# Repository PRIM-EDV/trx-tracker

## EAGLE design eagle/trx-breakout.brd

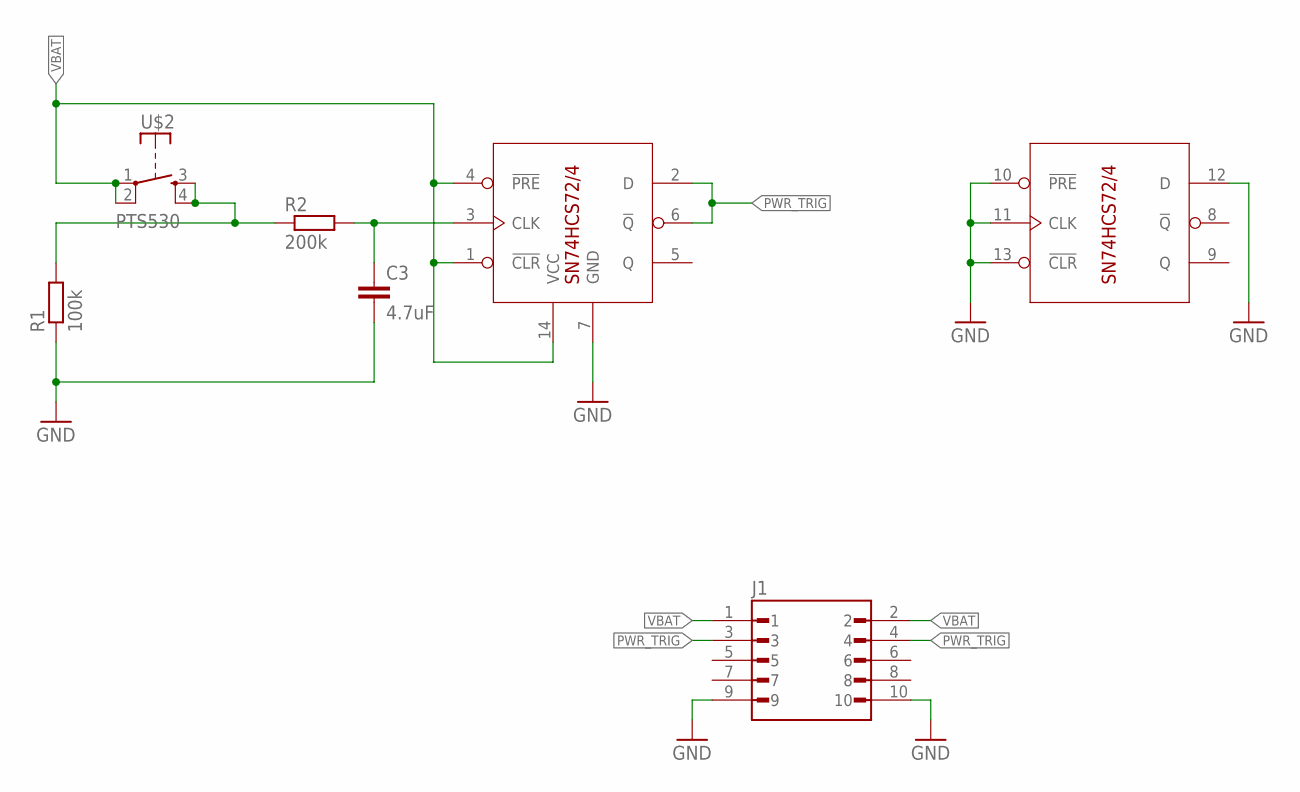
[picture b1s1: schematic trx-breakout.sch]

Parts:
C3: 4.7uF; C0805
J1: DF12NB(3.0)-10DX-0.5VHRS_DF12NB(3.0)-10DS-0.5V; HRS_DF12NB(3.0)-10DS-0.5V
R1: 100k; R0805
R2: 200k; R0805
U$1: SN74HCS72/4; TSSOP14
U$2: PTS530

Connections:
GND: C3.2, J1.9, J1.10, R1.1, U$1.7 (GND), U$1.10 (!PRE), U$1.11 (CLK), U$1.12 (D), U$1.13 (!CLR)
unnamed: C3.1, R2.2, U$1.3 (CLK)
unnamed: R1.2, R2.1, U$2.3 (S), U$2.4 (S)
PWR_TRIG: J1.3, J1.4, U$1.2 (D), U$1.6 (!Q)
VBAT: J1.1, J1.2, U$1.1 (!CLR), U$1.4 (!PRE), U$1.14 (VCC), U$2.1, U$2.2

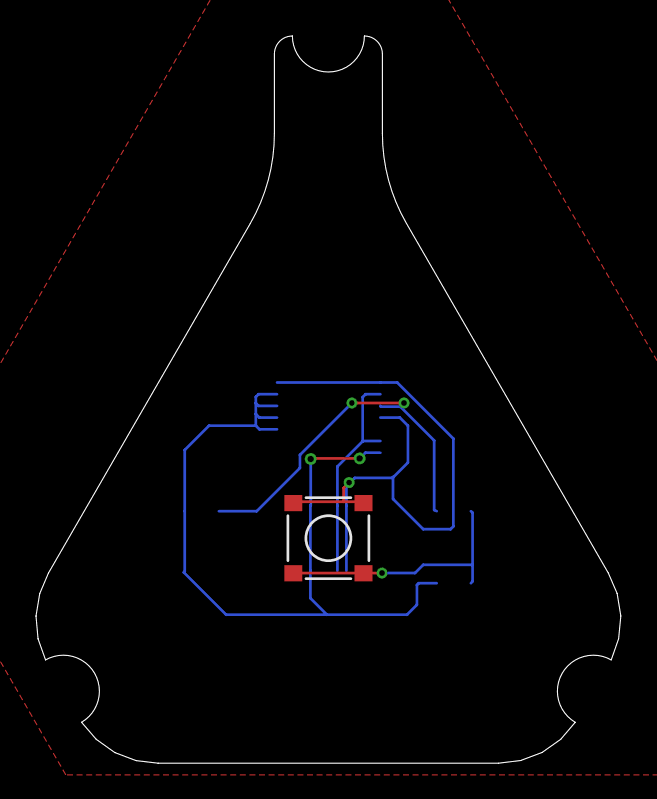
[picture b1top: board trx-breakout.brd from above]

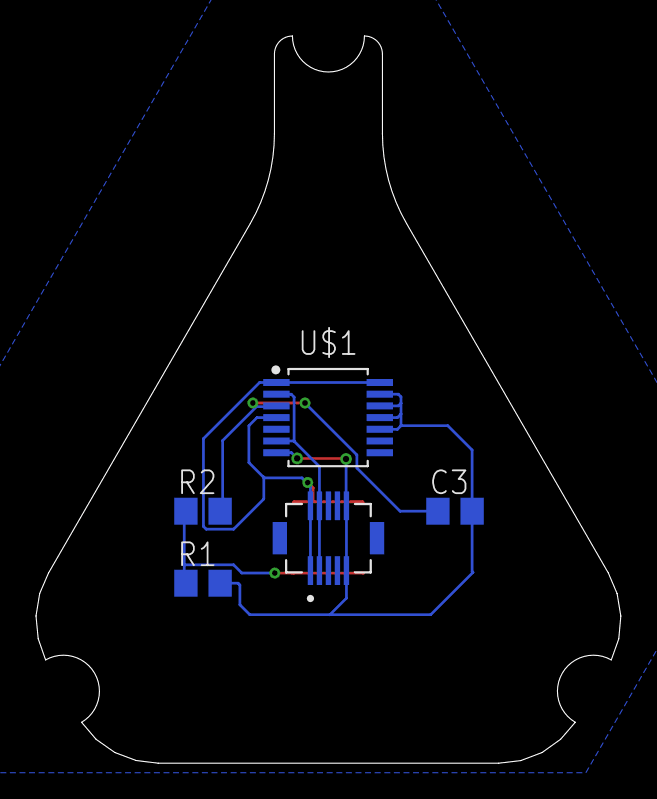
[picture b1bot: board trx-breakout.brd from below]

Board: 2 copper layers, 32.5 x 40.4 mm, 6 parts (5 on the bottom side), 5 nets.

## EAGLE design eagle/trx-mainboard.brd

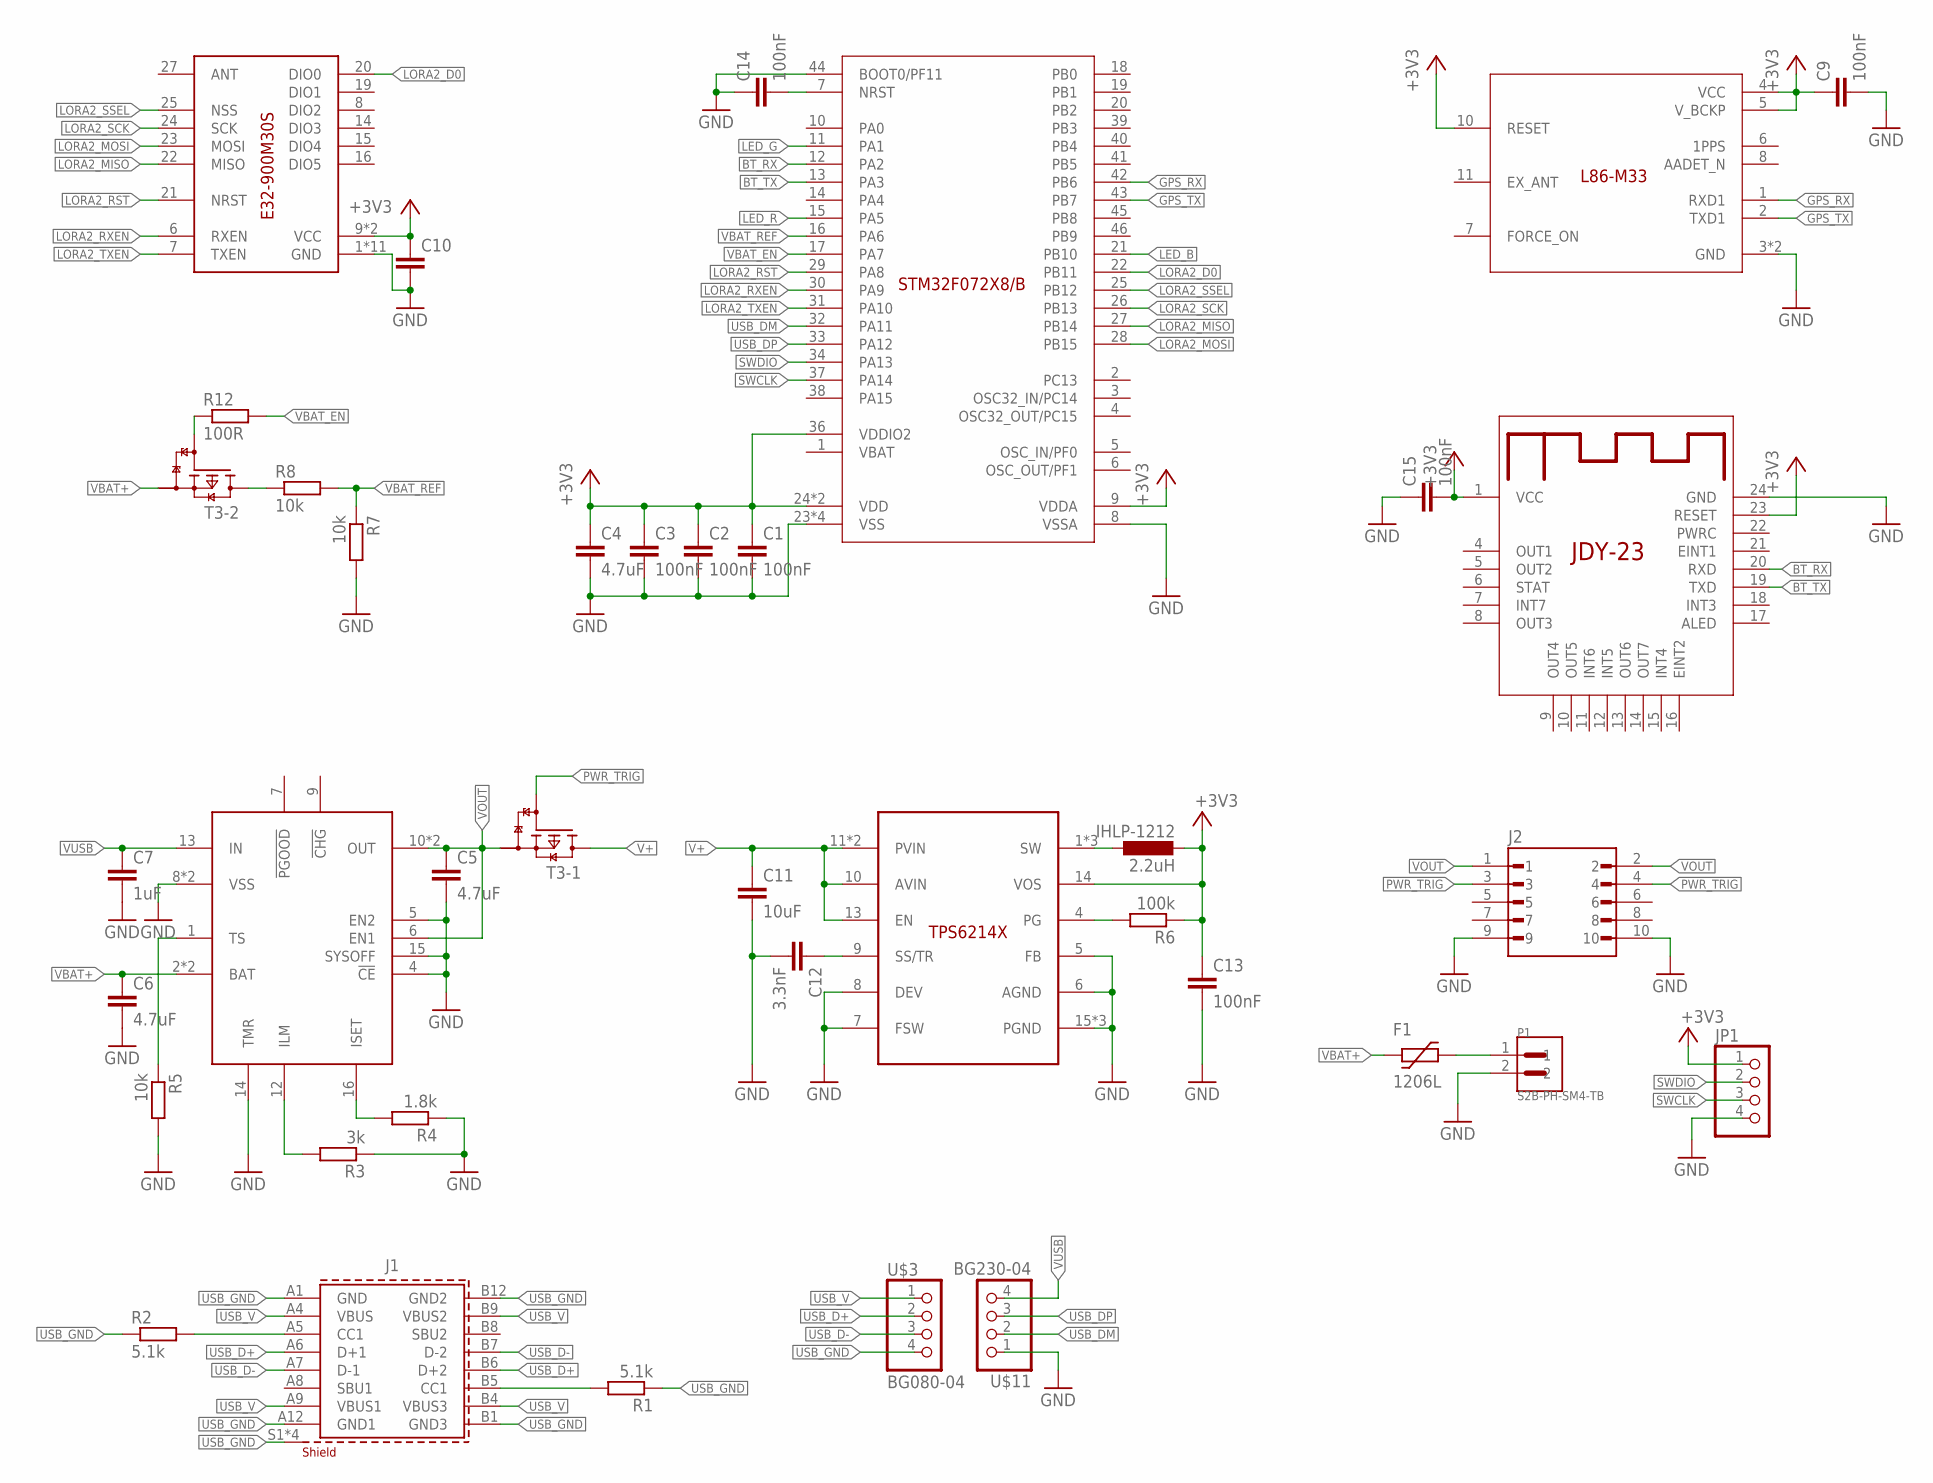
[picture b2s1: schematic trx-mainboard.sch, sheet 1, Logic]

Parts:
C1, C2, C3, C9, C13, C14, C15: 100nF; C0805
C4, C5, C6, C10: 4.7uF; C0805
C7: 1uF; C0805
C11: 10uF; C0805
C12: 3.3nF; C0805
F1: 1206L
J1: 629722000214
J2: DF12NB(3.0)-10DP-0.5V; HRS_DF12NB(3.0)-10DP-0.5V
JP1: PINHD-1X04_2.54-SMD; 1X04SMD
P1: S2B-PH-SM4-TB; JST_S2B-PH-SM4-TB
R1, R2: 5.1k; R0805
R3: 3k; R0805
R4: 1.8k; R0805
R5, R7, R8: 10k; R0805
R6: 100k; R0805
R12: 100R; R0805
T3: NX3008PBKS; SOT363
U2: BQ2407X; VQFN16-3X3
U$1: L86-M33
U$2: TPS6214X; VQFN16-3X3
U$3: BG080-04; P-1X4/90-2.54X1.50MMX2.54MM-SMT
U$4: IHLP-1212; 1212BZ
U$5: JDY-23
U$10: STM32-F072X8/B-48; UFQFPN48-7X7
U$11: BG230-04; S-1X4/90-2.54MM-SMT
U$14: E32-900M30S

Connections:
+3V3: C1.1, C2.1, C3.1, C4.1, C9.1, C10.1, C13.1, C15.2, JP1.1, R6.1, U$1.4 (VCC), U$1.5 (V_BCKP), U$1.10 (RESET), U$2.14 (VOS), U$4.2, U$5.1 (VCC), U$5.23 (RESET), U$10.9 (VDDA), U$10.24 (VDD), U$10.36 (VDDIO2), U$10.48 (VDD), U$14.9 (VCC), U$14.10 (VCC); also elsewhere on the board
BT_RX: U$5.20 (RXD), U$10.12 (PA2)
BT_TX: U$5.19 (TXD), U$10.13 (PA3)
GND: C1.2, C2.2, C3.2, C4.2, C5.2, C6.2, C7.2, C9.2, C10.2, C11.2, C12.2, C13.2, C14.1, C15.1, J2.9, J2.10, JP1.4, P1.2, R3.1, R4.1, R5.2, R7.2, U2.4 (!CE), U2.5 (EN2), U2.8 (VSS), U2.14 (TMR), U2.15 (SYSOFF), U2.17 (VSS), U$1.3 (GND), U$1.12 (GND), U$2.5 (FB), U$2.6 (AGND), U$2.7 (FSW), U$2.8 (DEV), U$2.15 (PGND), U$2.16 (PGND), U$2.17 (PGND), U$5.24 (GND), U$10.8 (VSSA), U$10.23 (VSS), U$10.35 (VSS), U$10.44 (BOOT0/PF11), U$10.47 (VSS), U$10.P$49 (VSS), U$11.1, U$14.1 (GND), U$14.2 (GND), U$14.3 (GND), U$14.4 (GND), U$14.5 (GND), U$14.11 (GND), U$14.12 (GND), U$14.17 (GND), U$14.18 (GND), U$14.26 (GND), U$14.28 (GND); also elsewhere on the board
GPS_RX: U$1.1 (RXD1), U$10.42 (PB6)
GPS_TX: U$1.2 (TXD1), U$10.43 (PB7)
LED_B: U$10.21 (PB10); also elsewhere on the board
LED_G: U$10.11 (PA1); also elsewhere on the board
LED_R: U$10.15 (PA5); also elsewhere on the board
LORA2_D0: U$10.22 (PB11), U$14.20 (DIO0)
LORA2_MISO: U$10.27 (PB14), U$14.22 (MISO)
LORA2_MOSI: U$10.28 (PB15), U$14.23 (MOSI)
LORA2_RST: U$10.29 (PA8), U$14.21 (NRST)
LORA2_RXEN: U$10.30 (PA9), U$14.6 (RXEN)
LORA2_SCK: U$10.26 (PB13), U$14.24 (SCK)
LORA2_SSEL: U$10.25 (PB12), U$14.25 (NSS)
LORA2_TXEN: U$10.31 (PA10), U$14.7 (TXEN)
unnamed: J1.A5 (CC1), R2.2
unnamed: J1.B5 (CC1), R1.2
unnamed: R3.2, U2.12 (ILM)
unnamed: R4.2, U2.16 (ISET)
unnamed: R5.1, U2.1 (TS)
unnamed: U$2.1 (SW), U$2.2 (SW), U$2.3 (SW), U$4.1
unnamed: C12.1, U$2.9 (SS/TR)
unnamed: R6.2, U$2.4 (PG)
unnamed: C14.2, U$10.7 (NRST)
unnamed: F1.P$2 (2), P1.1
unnamed: R8.1, T3.3 (D)
unnamed: R12.1, T3.5 (G)
PWR_TRIG: J2.3, J2.4, T3.2 (G)
SWCLK: JP1.3, U$10.37 (PA14)
SWDIO: JP1.2, U$10.34 (PA13)
USB_D+: J1.A6 (D+1), J1.B6 (D+2), U$3.2
USB_D-: J1.A7 (D-1), J1.B7 (D-2), U$3.3
USB_DM: U$10.32 (PA11), U$11.2
USB_DP: U$10.33 (PA12), U$11.3
USB_GND: J1.A1 (GND), J1.A12 (GND1), J1.B1 (GND3), J1.B12 (GND2), J1.S1 (SHIELD), J1.S2 (SHIELD), J1.S3 (SHIELD), J1.S4 (SHIELD), R1.1, R2.1, U$3.4
USB_V: J1.A4 (VBUS), J1.A9 (VBUS1), J1.B4 (VBUS3), J1.B9 (VBUS2), U$3.1
V+: C11.1, T3.6 (D), U$2.10 (AVIN), U$2.11 (PVIN), U$2.12 (PVIN), U$2.13 (EN)
VBAT+: C6.1, F1.P$1 (1), T3.4 (S), U2.2 (BAT), U2.3 (BAT)
VBAT_EN: R12.2, U$10.17 (PA7)
VBAT_REF: R7.1, R8.2, U$10.16 (PA6)
VOUT: C5.1, J2.1, J2.2, T3.1 (S), U2.6 (EN1), U2.10 (OUT), U2.11 (OUT)
VUSB: C7.1, U2.13 (IN), U$11.4

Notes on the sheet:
2.2uH

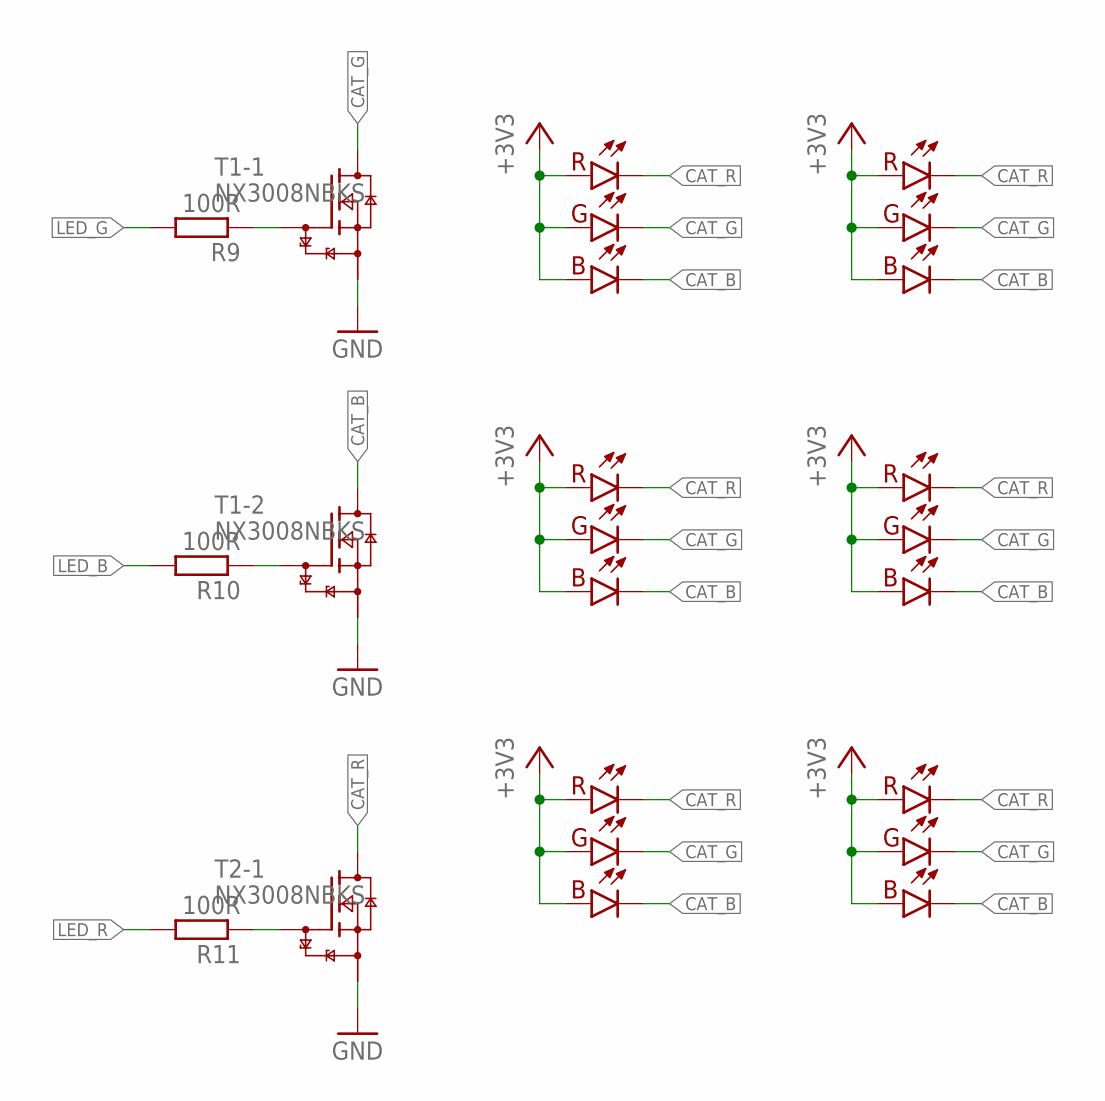
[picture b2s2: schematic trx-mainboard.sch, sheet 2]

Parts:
R9, R10, R11: 100R; R0805
T1, T2: NX3008NBKS; SOT363
U$6, U$7, U$8, U$9, U$12, U$13: RGB_LED; PLCC6

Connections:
+3V3: U$6.1 (A.B), U$6.3 (A.R), U$6.5 (A.G), U$7.1 (A.B), U$7.3 (A.R), U$7.5 (A.G), U$8.1 (A.B), U$8.3 (A.R), U$8.5 (A.G), U$9.1 (A.B), U$9.3 (A.R), U$9.5 (A.G), U$12.1 (A.B), U$12.3 (A.R), U$12.5 (A.G), U$13.1 (A.B), U$13.3 (A.R), U$13.5 (A.G); also elsewhere on the board
CAT_B: T1.3 (D), U$6.2 (C.B), U$7.2 (C.B), U$8.2 (C.B), U$9.2 (C.B), U$12.2 (C.B), U$13.2 (C.B)
CAT_G: T1.6 (D), U$6.6 (C.G), U$7.6 (C.G), U$8.6 (C.G), U$9.6 (C.G), U$12.6 (C.G), U$13.6 (C.G)
CAT_R: T2.6 (D), U$6.4 (C.R), U$7.4 (C.R), U$8.4 (C.R), U$9.4 (C.R), U$12.4 (C.R), U$13.4 (C.R)
GND: T1.1 (S), T1.4 (S), T2.1 (S); also elsewhere on the board
LED_B: R10.2; also elsewhere on the board
LED_G: R9.2; also elsewhere on the board
LED_R: R11.2; also elsewhere on the board
unnamed: R9.1, T1.2 (G)
unnamed: R10.1, T1.5 (G)
unnamed: R11.1, T2.2 (G)

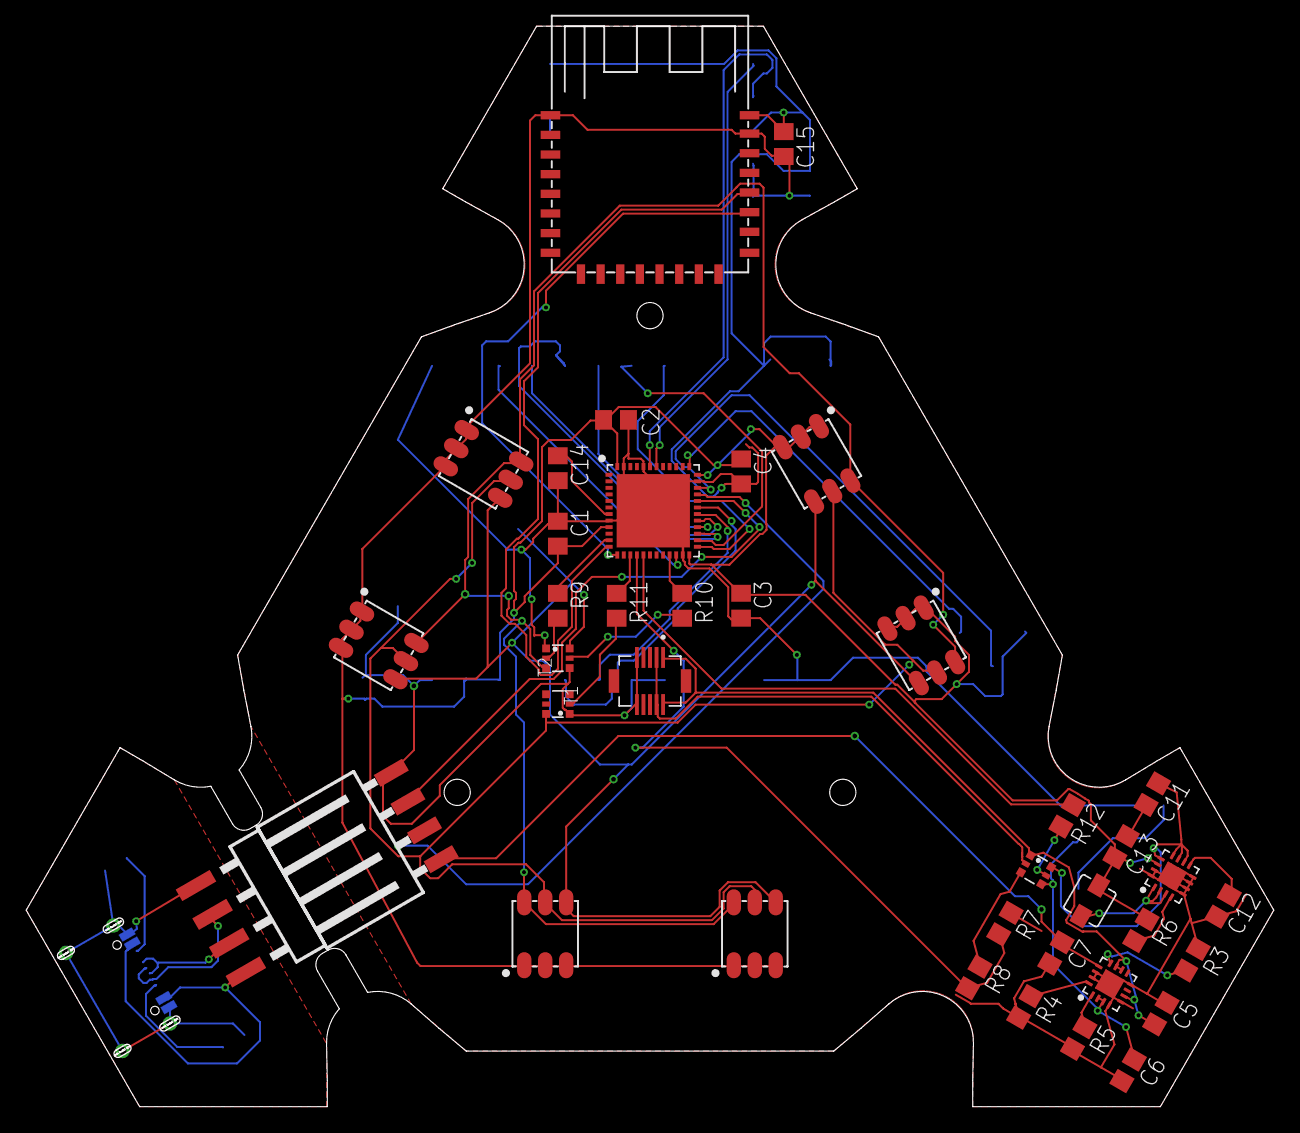
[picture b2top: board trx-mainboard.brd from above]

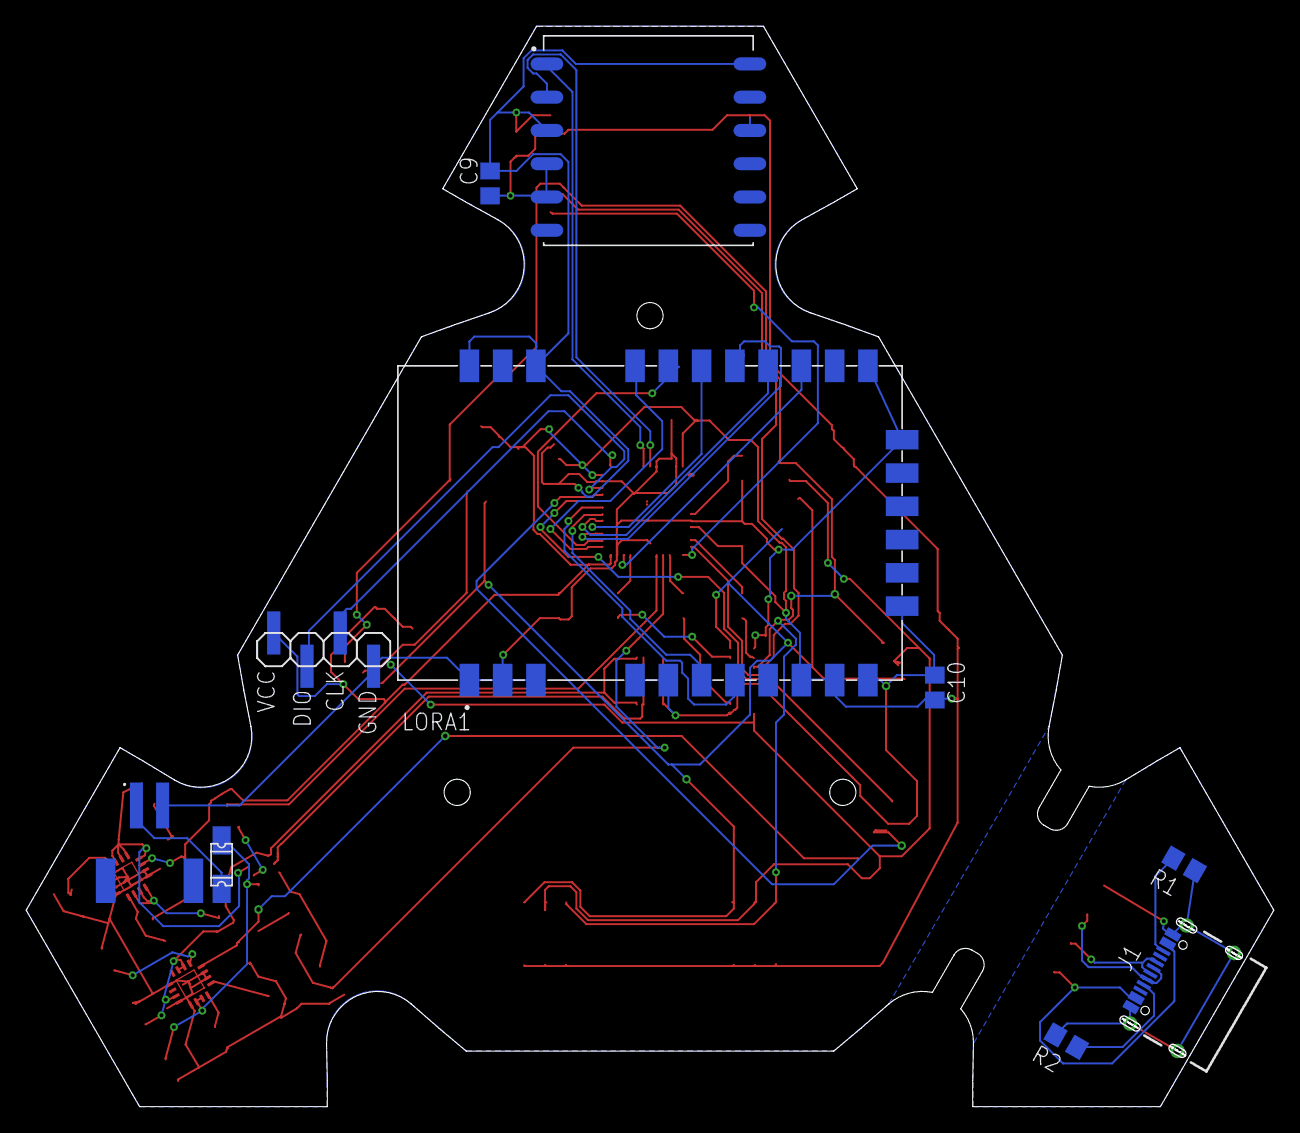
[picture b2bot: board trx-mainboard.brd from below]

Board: 2 copper layers, 95.2 x 82.4 mm, 49 parts (10 on the bottom side), 50 nets.

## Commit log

2022-09-17 Added initial dat
2023-05-01 Added eagle files and gitignore
2023-05-01 Added display pinheader
2023-05-02 Changed board layout
2023-05-08 Added further components to pcb
2023-07-02 Added breakout board and progressed mainboard
2023-07-02 updated modm
2023-07-04 Added basic auto-route
2023-07-16 Finalized alpha design
2023-08-17 Added firmware boilerplate
2023-08-17 Added new layout and gerber files
2023-08-20 Added basic usb serial implementation
2023-08-25 Designed new boards wit fixed errors
2023-08-25 Added basic functionality
2023-09-21 Reworked breakout board
2024-02-08 Modified board layout
2024-03-21 Adjusted settings for trx version
2024-03-26 Fixed Pin Settings and power control of E32 module
2024-05-01 Added wait to TX
2024-05-01 renamed lora namespace
2024-05-04 Added nanopb protocol boilerplate and led driver boilerplate
2024-05-05 Added preliminary led driver
2024-05-05 Added lora timeouts
2025-08-02 Added preliminary csma
2025-08-02 Added missing DIO mapping for CAD mode
2025-08-02 Added preliminary battery adc
2025-08-25 Added adc conversion for battery monitoring
2025-08-27 Added preliminary bluetooth gateway
2025-08-28 Prepared protobuf protocol implementation
2025-08-29 Added nanopb string decode callback

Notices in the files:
parts and their libraries:
Wurth_Connectors_WR-USB: Copyright: Würth Elektronik
NXP_60_26022015: This library may be distributed and adapted freely for any purpose, as long as NXP is credited and any new creation is licensed under the same terms.
